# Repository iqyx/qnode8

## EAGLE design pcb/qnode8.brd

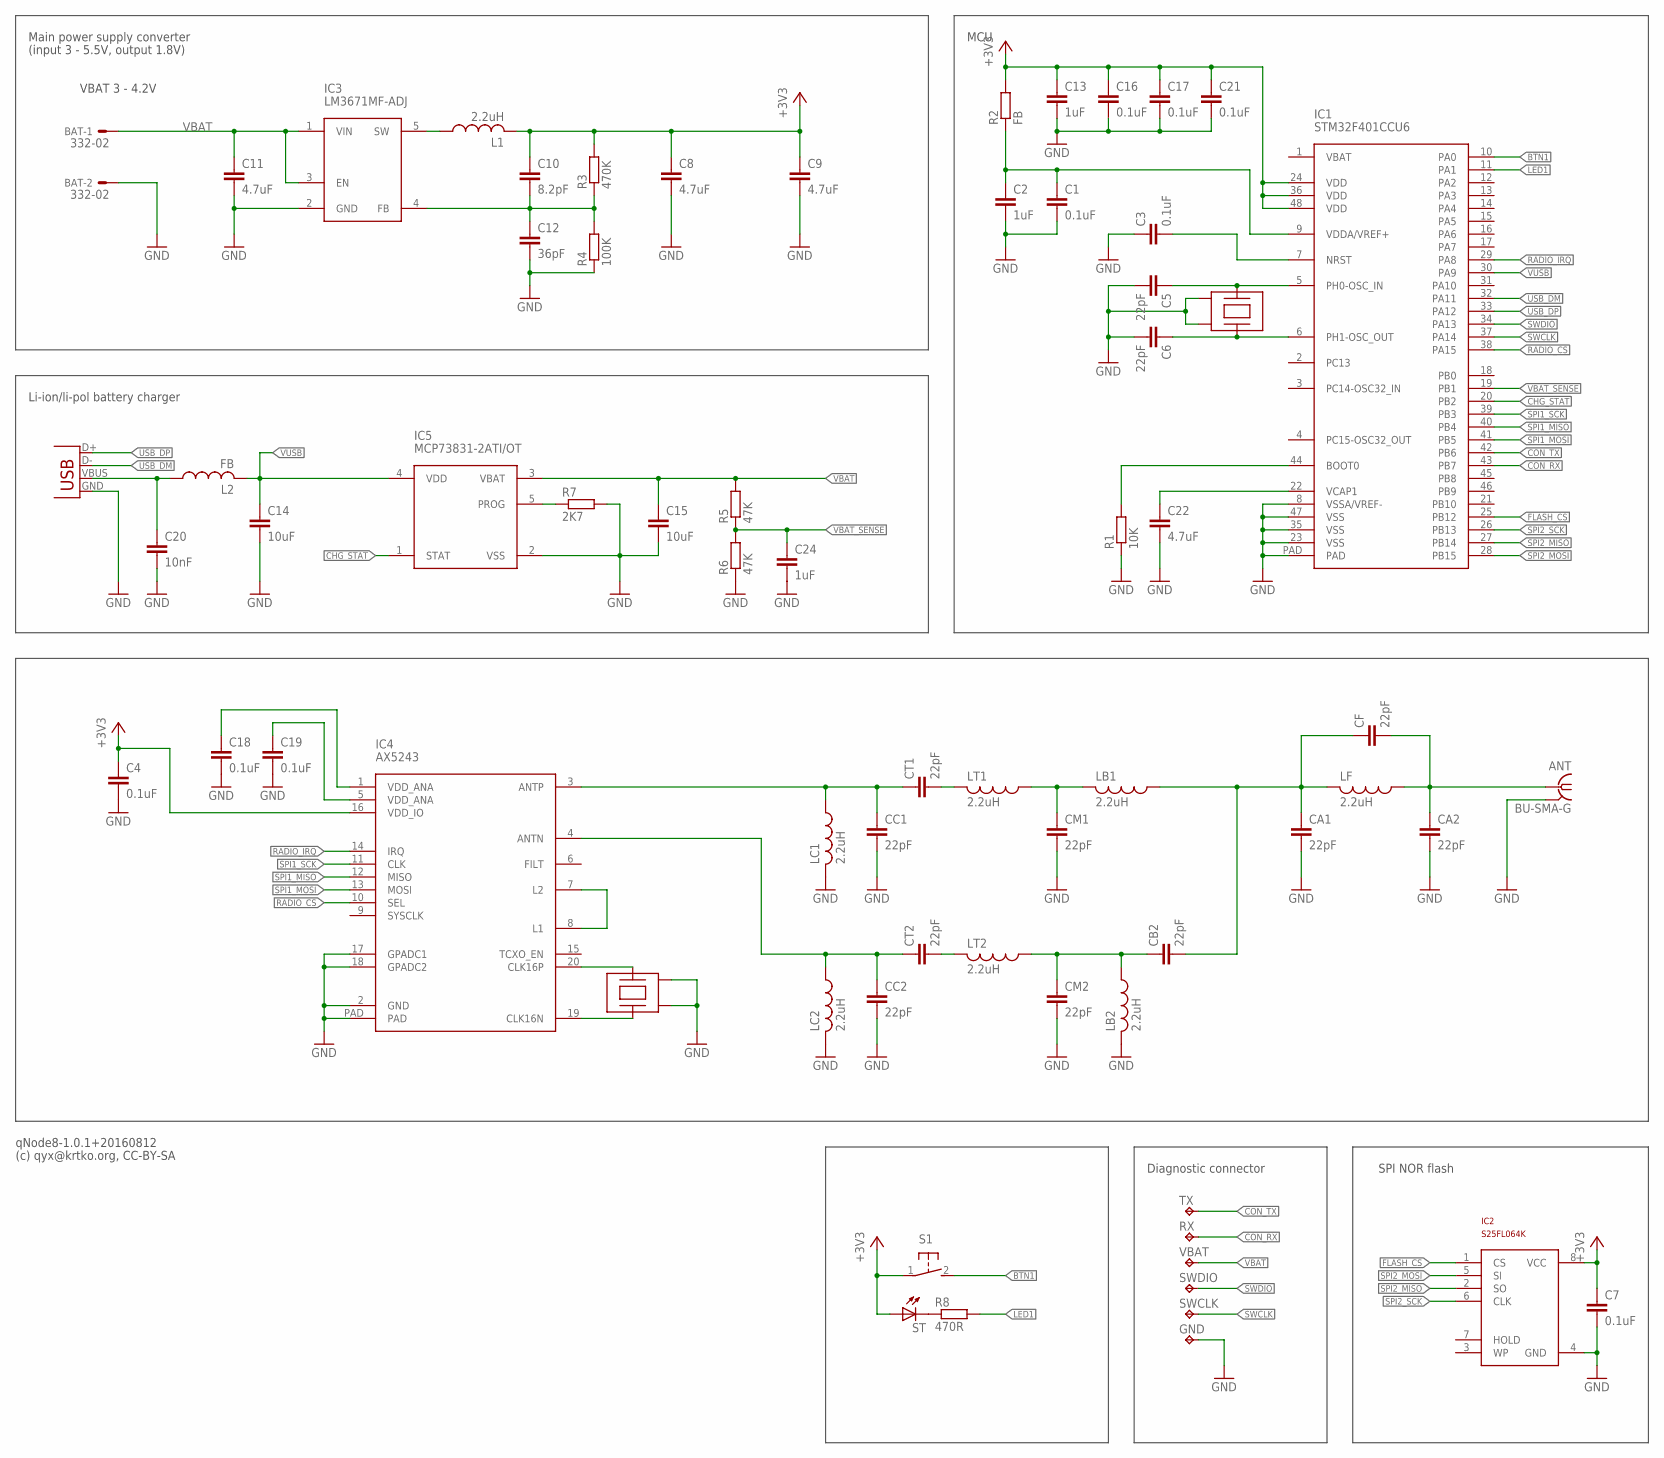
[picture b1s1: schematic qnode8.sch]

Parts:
ANT: BU-SMA-G
BAT: 332-02
C1, C3, C4, C7, C16, C17, C18, C19, C21: 0.1uF; C0603
C2, C13, C24: 1uF; C0603
C5, C6: 22pF; C0603
C8, C9, C11: 4.7uF; C0805
C10: 8.2pF; C0603
C12: 36pF; C0603
C14, C15: 10uF; C1206
C20: 10nF; C0603
C22: 4.7uF; C0603
CA1, CA2: 22pF; C0603
CB2: 22pF; C0603
CC1, CC2: 22pF; C0603
CF: 22pF; C0603
CM1, CM2: 22pF; C0603
CT1, CT2: 22pF; C0603
GND: TPB2,54; B2,54
IC1: STM32F401CCU6; UFQFPN48
IC2: S25FL064K; SO-08M
IC3: LM3671MF-ADJ; SOT23-5
IC4: AX5243; QFN20
IC5: MCP73831-2ATI/OT; SOT23-5
L1: 2.2uH; L2012C
L2: FB; L2012C
LB1, LB2: 2.2uH; L2012C
LC1, LC2: 2.2uH; L2012C
LF: 2.2uH; L2012C
LT1, LT2: 2.2uH; L2012C
R1: 10K; R0603
R2: FB; R0603
R3: 470K; R0603
R4: 100K; R0603
R5, R6: 47K; R0603
R7: 2K7; R0603
R8: 470R; R0603
RX: TPB2,54; B2,54
S1: 31-XX; B3F-31XX
ST: LED3MM
SWCLK: TPB2,54; B2,54
SWDIO: TPB2,54; B2,54
TX: TPB2,54; B2,54
USB: USB-MICROB
VBAT: TPB2,54; B2,54
X1, X2: XTAL-7M; XTAL_7M

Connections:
+3V3: C4.1, C7.1, C8.1, C9.1, C10.1, C13.1, C16.1, C17.1, C21.1, IC1.24 (VDD), IC1.36 (VDD), IC1.48 (VDD), IC2.8 (VCC), IC4.16 (VDD_IO), L1.2, R2.2, R3.2, S1.1, ST.A
BTN1: IC1.10 (PA0), S1.2 (S)
CHG_STAT: IC1.20 (PB2), IC5.1 (STAT)
CON_RX: IC1.43 (PB7), RX.TP
CON_TX: IC1.42 (PB6), TX.TP
FLASH_CS: IC1.25 (PB12), IC2.1 (CS)
GND: ANT.2, ANT.3 (2), ANT.4 (2), ANT.5 (2), BAT.2, C1.2, C2.2, C3.1, C4.2, C5.2, C6.2, C7.2, C8.2, C9.2, C11.2, C12.2, C13.2, C14.2, C15.2, C16.2, C17.2, C18.2, C19.2, C20.2, C21.2, C22.2, C24.2, CA1.2, CA2.2, CC1.2, CC2.2, CM1.2, CM2.2, GND.TP, IC1.8 (VSSA/VREF-), IC1.23 (VSS), IC1.35 (VSS), IC1.47 (VSS), IC1.PAD, IC2.4 (GND), IC3.2 (GND), IC4.2 (GND), IC4.17 (GPADC1), IC4.18 (GPADC2), IC4.PAD, IC5.2 (VSS), LB2.2, LC1.2, LC2.2, R1.1, R4.1, R6.1, R7.2, USB.GND, X1.2 (G1), X1.4 (G2), X2.2 (G1), X2.4 (G2)
LED1: IC1.11 (PA1), R8.2
unnamed: IC1.44 (BOOT0), R1.2
unnamed: C1.1, C2.1, IC1.9 (VDDA/VREF+), R2.1
unnamed: IC3.5 (SW), L1.1
unnamed: IC5.5 (PROG), R7.1
unnamed: C22.1, IC1.22 (VCAP1)
unnamed: C3.2, IC1.7 (NRST)
unnamed: C10.2, C12.1, IC3.4 (FB), R3.1, R4.2
unnamed: C5.1, IC1.5 (PH0-OSC_IN), X1.1
unnamed: C6.1, IC1.6 (PH1-OSC_OUT), X1.3 (2)
unnamed: CC1.1, CT1.1, IC4.3 (ANTP), LC1.1
unnamed: CC2.1, CT2.1, IC4.4 (ANTN), LC2.1
unnamed: IC4.7 (L2), IC4.8 (L1)
unnamed: CA1.1, CB2.2, CF.1, LB1.1, LF.2
unnamed: ANT.1, CA2.1, CF.2, LF.1
unnamed: CT1.2, LT1.2
unnamed: CM1.1, LB1.2, LT1.1
unnamed: CT2.2, LT2.2
unnamed: CB2.1, CM2.1, LB2.1, LT2.1
unnamed: C18.1, IC4.1 (VDD_ANA)
unnamed: IC4.19 (CLK16N), X2.3 (2)
unnamed: IC4.20 (CLK16P), X2.1
unnamed: C19.1, IC4.5 (VDD_ANA)
unnamed: R8.1, ST.K (C)
RADIO_CS: IC1.38 (PA15), IC4.10 (SEL)
RADIO_IRQ: IC1.29 (PA8), IC4.14 (IRQ)
SPI1_MISO: IC1.40 (PB4), IC4.12 (MISO)
SPI1_MOSI: IC1.41 (PB5), IC4.13 (MOSI)
SPI1_SCK: IC1.39 (PB3), IC4.11 (CLK)
SPI2_MISO: IC1.27 (PB14), IC2.2 (SO)
SPI2_MOSI: IC1.28 (PB15), IC2.5 (SI)
SPI2_SCK: IC1.26 (PB13), IC2.6 (CLK)
SWCLK: IC1.37 (PA14), SWCLK.TP
SWDIO: IC1.34 (PA13), SWDIO.TP
USB_DM: IC1.32 (PA11), USB.D-
USB_DP: IC1.33 (PA12), USB.D+
USB_VBUS: C20.1, L2.1, USB.VBUS
VBAT: BAT.1, C11.1, C15.1, IC3.1 (VIN), IC3.3 (EN), IC5.3 (VBAT), R5.2, VBAT.TP
VBAT_SENSE: C24.1, IC1.19 (PB1), R5.1, R6.2
VUSB: C14.1, IC1.30 (PA9), IC5.4 (VDD), L2.2

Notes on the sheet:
VBAT 3 - 4.2V
Li-ion/li-pol battery charger
Main power supply converter
(input 3 - 5.5V, output 1.8V)
SPI NOR flash
MCU
Diagnostic connector
qNode8-1.0.1+20160812
(c) qyx@krtko.org, CC-BY-SA

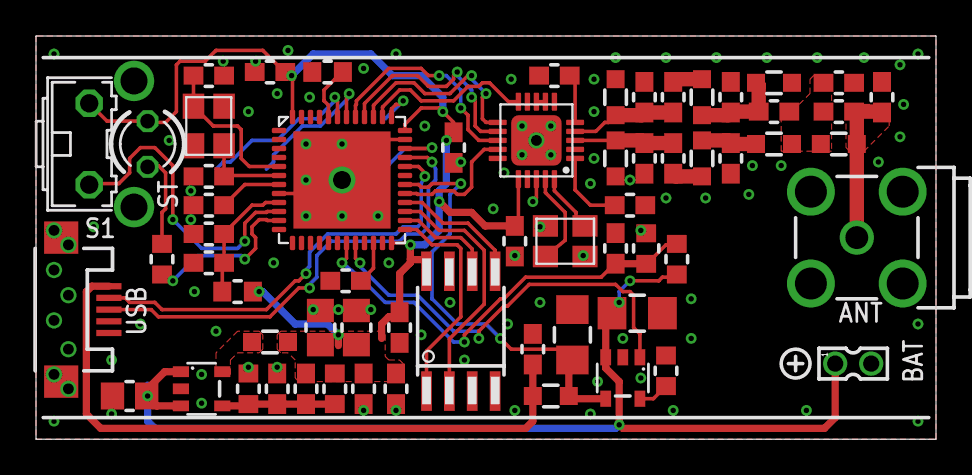
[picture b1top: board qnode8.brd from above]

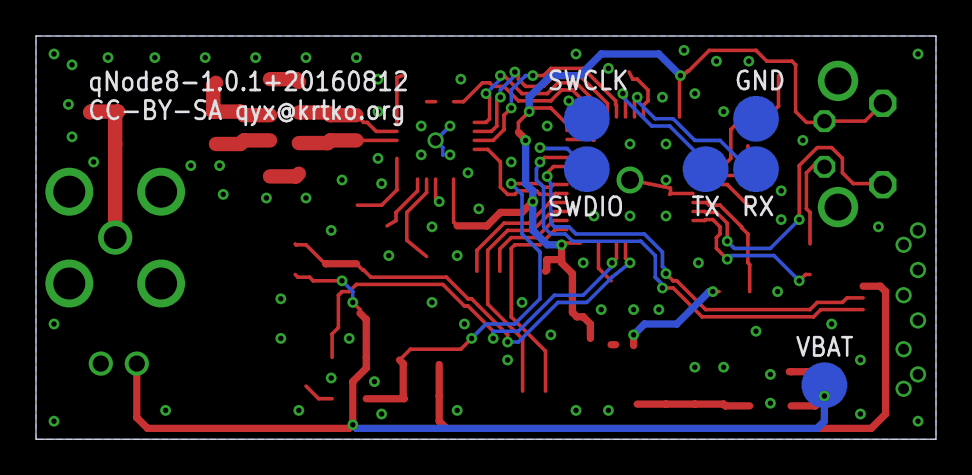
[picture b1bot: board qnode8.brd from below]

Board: 2 copper layers, 50.0 x 22.4 mm, 68 parts (6 on the bottom side), 47 nets.

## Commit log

2016-08-10 Add .gitignore
2016-08-10 Add initial version of schematic and layout
2016-08-11 Finish schematic and board layout
2016-08-12 Fix unconnected USB_VBUS

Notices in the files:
pcb/qnode8.brd:
CC-BY-SA qyx@krtko.org
